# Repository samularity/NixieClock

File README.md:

# NixieClock
We (exco, kist, makefu and me) try to create a modular opensource nixie clock
The clock is based on a atmega32u4 esp8266 , there will be optional i²c rtc chip for good time accuray.

There will be three types of Modules
- HV Supply Module (contains max1771 stepup for generating Tube supply voltage)
- Controller Module (contains ESP8266 and RTC)
- Nixie Module (Contains 2 Nixies and two Attiny2313 i²c slaves)

maybe you find some additional information here
https://wiki.euer.krebsco.de/samu.html#nixie
https://excogitation.de/wiki/#IN-12A%20nixie%20clock

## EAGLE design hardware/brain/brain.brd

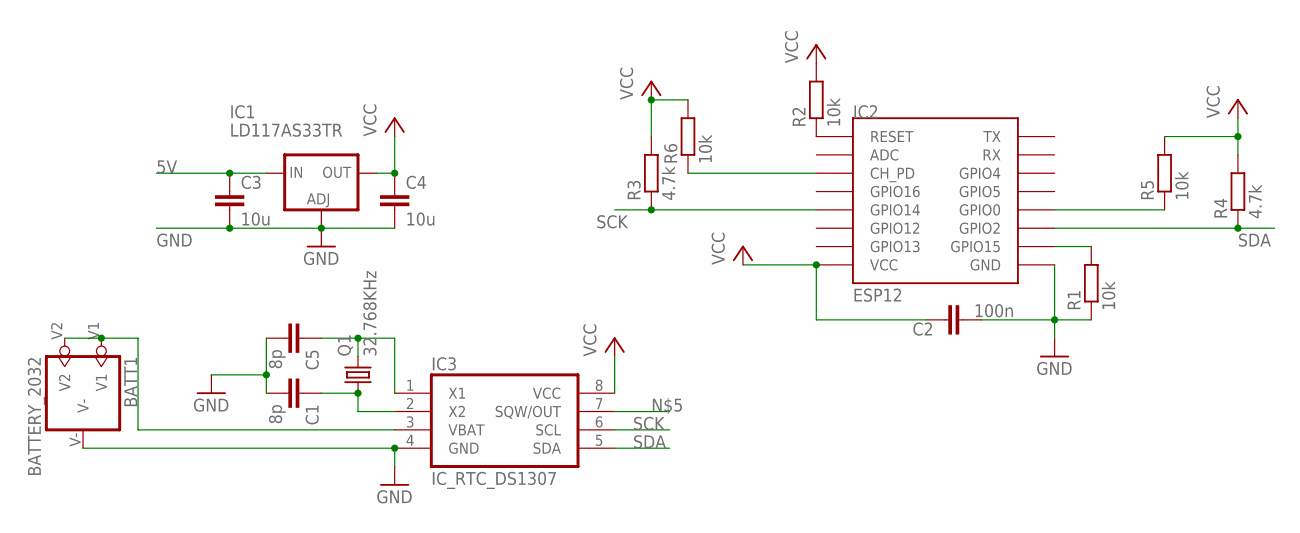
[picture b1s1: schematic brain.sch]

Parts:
BATT1: BATTERY_2032; BATT2032
C1, C5: 8p; C0805
C2: 100n; C0805
C3, C4: 10u; C0805
IC1: LD117AS33TR; SOT223
IC2: ESP12
IC3: IC_RTC_DS1307; SO-8
Q1: 32.768KHz; TC26H
R1, R2, R5, R6: 10k; R0805
R3, R4: 4.7k; R0805

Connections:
5V: C3.1, IC1.3 (IN)
BOOTMODE: IC2.GPIO0, R5.1
GND: BATT1.V-, C1.2, C2.2, C3.2, C4.2, C5.2, IC1.1 (ADJ), IC2.GND, IC3.4 (GND), R1.1
unnamed: IC2.RESET, R2.1
unnamed: IC2.GPIO15, R1.2
unnamed: IC2.CH_PD, R6.1
unnamed: C5.1, IC3.1 (X1), Q1.2
unnamed: BATT1.V1, BATT1.V2, IC3.3 (VBAT)
unnamed: C1.1, IC3.2 (X2), Q1.1
SCK: IC2.GPIO14, IC3.6 (SCL), R3.1
SDA: IC2.GPIO2, IC3.5 (SDA), R4.1
VCC: C2.1, C4.1, IC1.4 (OUT), IC2.VCC, IC3.8 (VCC), R2.2, R3.2, R4.2, R5.2, R6.2

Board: 2 copper layers, 16 parts (0 on the bottom side), 12 nets, no tracks yet.

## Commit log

2015-03-13 inital commit
2015-03-13 further explanatioin
2015-03-20 initial commit of i²c slave source
    initial commit of attiny2313 i²c slave source
2015-03-20 add more doku stuff
    first plans of the connection system
2015-03-20 updated hardware setup
    removed atmega32u4
2015-03-22 inital commit of brain board, added libary for esp, all other parts are standard eagle parts
2015-03-23 add rtc
2015-03-23 add delay to ensure reading the correct address
2015-03-23 added nixieboard
2015-03-23 modified portpins
2015-03-23 edit pin settings, add ch_pd pullup
2015-03-25 cleanup add more doku/pinout
2015-04-29 add wiki links
2016-03-11 inital commit of lua demo code
2016-03-21 added connectors to nixieboard for stability
2016-06-21 add support for dots, change I2C base adress to 0x10, fix write adress issue
2016-11-01 added clock dots
2016-11-01 fixed dot distances
2017-04-27 fix DP IN-12A Pinout
2017-06-13 esp: init debugging
2017-06-13 gettime: init
2017-06-13 i2c: rm
2017-06-22 Fix Pinout to match actual Hardware PCBs
2017-06-27 add more debugging code
2017-06-28 Fix Wiki Link
    closes #1
2017-08-29 add test-code
2017-08-29 final: init
2017-08-29 update debugging
2017-11-16 fix mapping
2018-03-01 use new firmware
2018-03-01 add new firmware
2019-08-30 add boot delay and debug startup
